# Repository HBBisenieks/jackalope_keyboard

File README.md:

# Jackalope Keyboard

`NOTE:` Current source was built against `ergogen@3.1.1` and will not work with the `4.0.0` release (or newer).

A 50-key ergonomic ~(currently single-piece)~ single-piece or split column-staggered keyboard ~(with a split version planned for the future???)~ inspired by the Absolem, Kryia, and Iris.

The Jackalope layout is focussed on maximizing comfort for the thumbs and reducing reach for the fingers.

## To-Do:
- [x] Finalize prototype PCBs
- [ ] Verify PCBs
- [ ] BOM and build guide
- [ ] Default firmware

## Firmware
The Jackalope can run either [QMK](https://github.com/HBBisenieks/qmk_firmware/tree/jackalope_boards/keyboards/jackalope) 
with a pro-micro or KMK with a KB2040. Default keymap is still a work-in-progress pending 
actual hardware testing.

## Images
Renders of the left and right split PCBs:

## Old images of first-generation monoblock PCB and layout

Built using [Ergogen](https://ergogen.xyz/#).

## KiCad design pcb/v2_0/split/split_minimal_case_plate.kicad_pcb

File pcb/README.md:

# PCBs
The current revision of the boards, both split and monoblock, are under `v2_0/`. As previously, 
these boards are theoretically functional but untested, pending both firmware authoring (QMK and 
KMK support planned) and arrival of the prototype boards from JLCPCB.

## To-Do:
- [ ] Write QMK code
- [ ] Write KMK code
- [ ] Verify PCBs
- [ ] Build guide
- [ ] BOM

~The current revision of PCB uploaded to GH is routed but untested and reflects an older revision of the code than what's available in the base of the repo. It _might_ work, but I honestly put it together to learn a bit more about using KiCad than anything else and haven't yet tested the outline, so, you know, caveat emptor.~

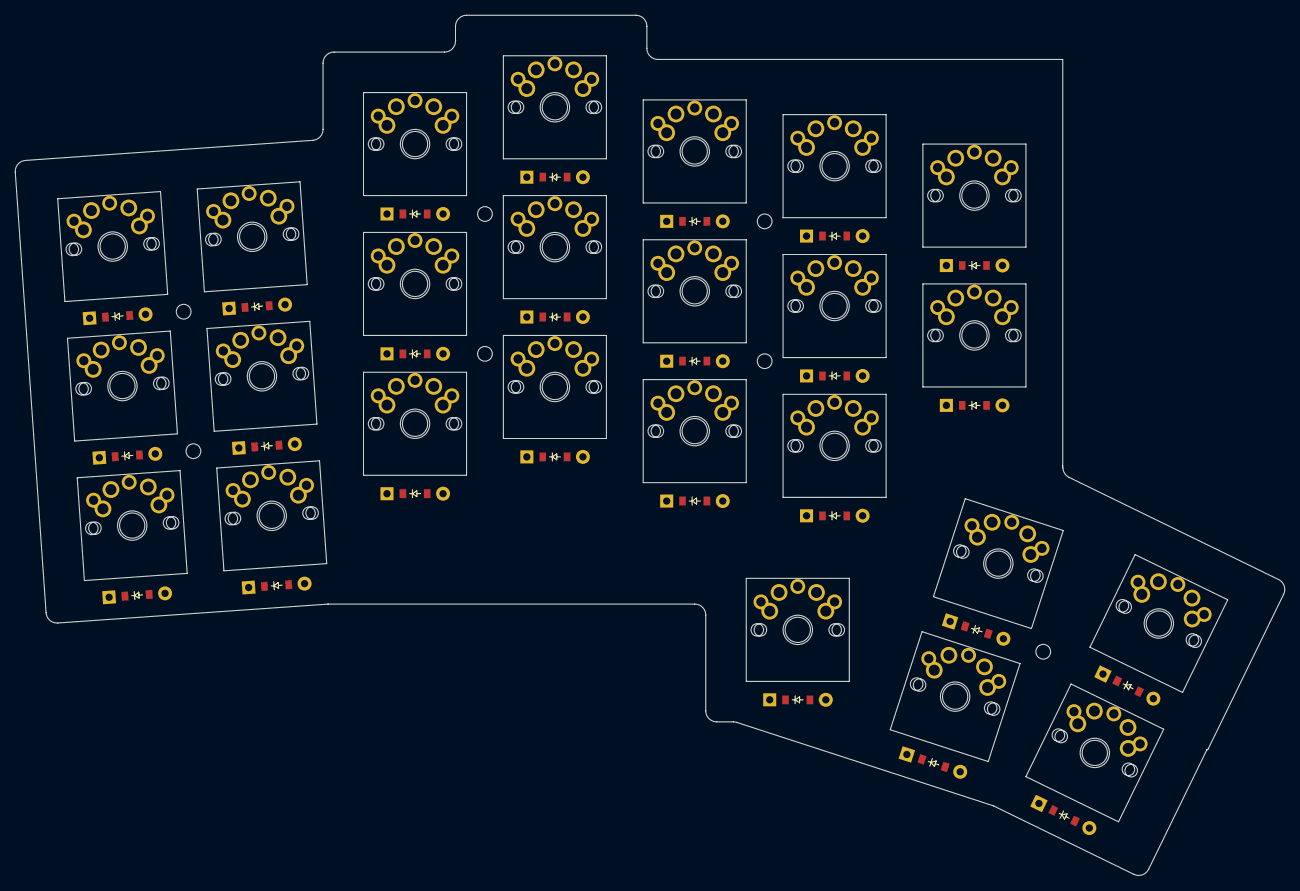
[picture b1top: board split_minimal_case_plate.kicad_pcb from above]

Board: 2 copper layers, 172.5 x 116.9 mm, 75 parts (0 on the bottom side), 36 nets, no tracks yet.

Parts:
D1, D2, D3, D4, D5, D6, D7, D8, D9, D10, D11, D12, D13, D14, D15, D16, D17, D18, D19, D20, D21, D22, D23, D24, D25: ComboDiode
S1, S3, S5, S7, S9, S11, S13, S15, S17, S19, S21, S23, S25, S27, S29, S31, S33, S35, S37, S39, S41, S43, S45, S47, S49: MX
S2, S4, S6, S8, S10, S12, S14, S16, S18, S20, S22, S24, S26, S28, S30, S32, S34, S36, S38, S40, S42, S44, S46, S48, S50: PG1350

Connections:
P0: S7.2, S8.2, S9.2, S10.2, S11.2, S12.2
P1: S1.2, S2.2, S3.2, S4.2, S5.2, S6.2
P2: S13.2, S14.2, S15.2, S16.2, S17.2, S18.2, S41.2, S42.2
P3: S19.2, S20.2, S21.2, S22.2, S23.2, S24.2, S43.2, S44.2
P4: S25.2, S26.2, S27.2, S28.2, S29.2, S30.2, S47.2, S48.2
P5: S31.2, S32.2, S33.2, S34.2, S35.2, S36.2, S45.2, S46.2
P6: S37.2, S38.2, S39.2, S40.2, S49.2, S50.2
P7: D3.1, D3.2, D6.1, D6.2, D9.1, D9.2, D12.1, D12.2, D15.1, D15.2, D18.1, D18.2, D20.1, D20.2
P8: D2.1, D2.2, D5.1, D5.2, D8.1, D8.2, D11.1, D11.2, D14.1, D14.2, D17.1, D17.2, D19.1, D19.2
P9: D1.1, D1.2, D4.1, D4.2, D7.1, D7.2, D10.1, D10.2, D13.1, D13.2, D16.1, D16.2
P10: D21.1, D21.2, D22.1, D22.2, D23.1, D23.2, D24.1, D24.2, D25.1, D25.2
home_lower: D24.1, D24.2, S47.1, S48.1
home_upper: D22.1, D22.2, S43.1, S44.1
index_bottom: D13.1, D13.2, S25.1, S26.1
index_home: D14.1, D14.2, S27.1, S28.1
index_top: D15.1, D15.2, S29.1, S30.1
inner_bottom: D16.1, D16.2, S31.1, S32.1
inner_home: D17.1, D17.2, S33.1, S34.1
inner_top: D18.1, D18.2, S35.1, S36.1
inner_upper: D21.1, D21.2, S41.1, S42.1
macro_home: D19.1, D19.2, S37.1, S38.1
macro_top: D20.1, D20.2, S39.1, S40.1
middle_bottom: D10.1, D10.2, S19.1, S20.1
middle_home: D11.1, D11.2, S21.1, S22.1
middle_top: D12.1, D12.2, S23.1, S24.1
outer_bottom: D1.1, D1.2, S1.1, S2.1
outer_home: D2.1, D2.2, S3.1, S4.1
outer_lower: D25.1, D25.2, S49.1, S50.1
outer_top: D3.1, D3.2, S5.1, S6.1
outer_upper: D23.1, D23.2, S45.1, S46.1
pinky_bottom: D4.1, D4.2, S7.1, S8.1
pinky_home: D5.1, D5.2, S9.1, S10.1
pinky_top: D6.1, D6.2, S11.1, S12.1
ring_bottom: D7.1, D7.2, S13.1, S14.1
ring_home: D8.1, D8.2, S15.1, S16.1
ring_top: D9.1, D9.2, S17.1, S18.1

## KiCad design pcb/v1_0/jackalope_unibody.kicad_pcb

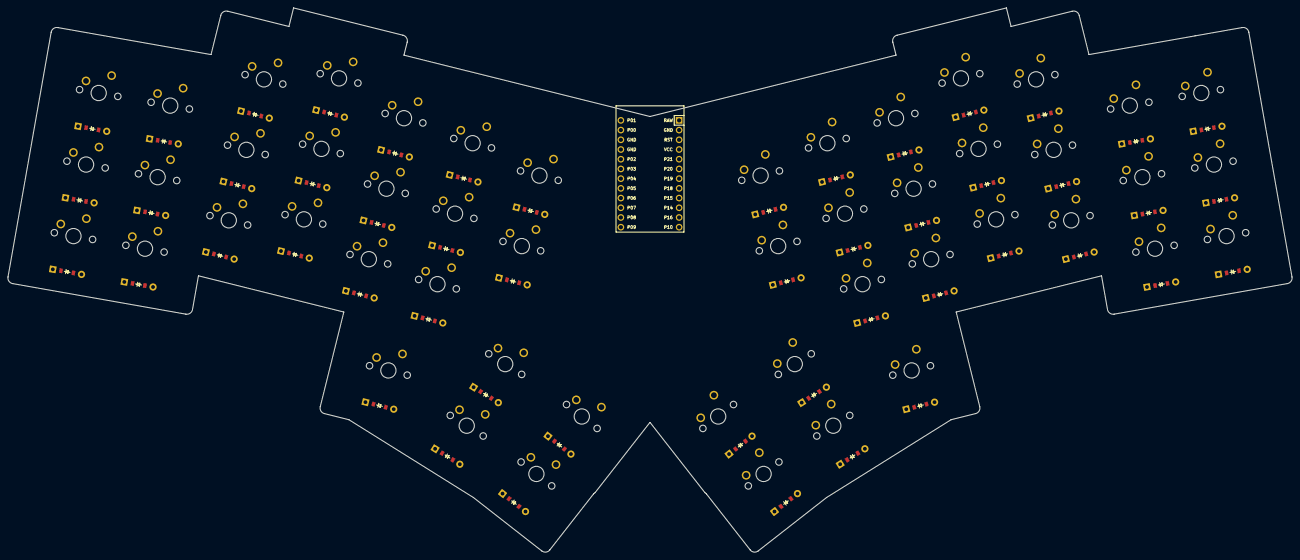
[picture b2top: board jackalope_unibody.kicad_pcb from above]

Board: 2 copper layers, 335.9 x 142.3 mm, 101 parts (0 on the bottom side), 69 nets, no tracks yet.

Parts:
D1, D2, D3, D4, D5, D6, D7, D8, D9, D10, D11, D12, D13, D14, D15, D16, D17, D18, D19, D20, D21, D22, D23, D24, D25, D26, D27, D28, D29, D30, D31, D32, D33, D34, D35, D36, D37, D38, D39, D40, D41, D42, D43, D44, D45, D46, D47, D48, D49, D50: ComboDiode
MCU1: ProMicro
S1, S2, S3, S4, S5, S6, S7, S8, S9, S10, S11, S12, S13, S14, S15, S16, S17, S18, S19, S20, S21, S22, S23, S24, S25, S26, S27, S28, S29, S30, S31, S32, S33, S34, S35, S36, S37, S38, S39, S40, S41, S42, S43, S44, S45, S46, S47, S48, S49, S50: MX

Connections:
GND: MCU1.2, MCU1.15, MCU1.16
P0: MCU1.14, S4.2, S5.2, S6.2
P1: MCU1.13, S1.2, S2.2, S3.2
P2: MCU1.17, S7.2, S8.2, S9.2, S21.2
P3: MCU1.18, S10.2, S11.2, S12.2, S22.2
P4: MCU1.19, S13.2, S14.2, S15.2, S24.2
P5: MCU1.20, S16.2, S17.2, S18.2, S23.2
P6: MCU1.21, S19.2, S20.2, S25.2
P7: D3.1, D3.2, D6.1, D6.2, D9.1, D9.2, D12.1, D12.2, D15.1, D15.2, D18.1, D18.2, D20.1, D20.2, D28.1, D28.2, D31.1, D31.2, D34.1, D34.2, D37.1, D37.2, D40.1, D40.2, D43.1, D43.2, D45.1, D45.2, MCU1.22
P8: D2.1, D2.2, D5.1, D5.2, D8.1, D8.2, D11.1, D11.2, D14.1, D14.2, D17.1, D17.2, D19.1, D19.2, D27.1, D27.2, D30.1, D30.2, D33.1, D33.2, D36.1, D36.2, D39.1, D39.2, D42.1, D42.2, D44.1, D44.2, MCU1.23
P9: D1.1, D1.2, D4.1, D4.2, D7.1, D7.2, D10.1, D10.2, D13.1, D13.2, D16.1, D16.2, D26.1, D26.2, D29.1, D29.2, D32.1, D32.2, D35.1, D35.2, D38.1, D38.2, D41.1, D41.2, MCU1.24
P10: D21.1, D21.2, D22.1, D22.2, D23.1, D23.2, D24.1, D24.2, D25.1, D25.2, D46.1, D46.2, D47.1, D47.2, D48.1, D48.2, D49.1, D49.2, D50.1, D50.2, MCU1.12
P14: MCU1.10, S41.2, S42.2, S43.2, S48.2
P15: MCU1.9, S38.2, S39.2, S40.2, S49.2
P16: MCU1.11, S44.2, S45.2, S50.2
P18: MCU1.8, S35.2, S36.2, S37.2, S47.2
P19: MCU1.7, S32.2, S33.2, S34.2, S46.2
P20: MCU1.6, S29.2, S30.2, S31.2
P21: MCU1.5, S26.2, S27.2, S28.2
home_lower: D24.1, D24.2, S24.1
home_upper: D22.1, D22.2, S22.1
index_bottom: D13.1, D13.2, S13.1
index_home: D14.1, D14.2, S14.1
index_top: D15.1, D15.2, S15.1
inner_bottom: D16.1, D16.2, S16.1
inner_home: D17.1, D17.2, S17.1
inner_top: D18.1, D18.2, S18.1
inner_upper: D21.1, D21.2, S21.1
macro_home: D19.1, D19.2, S19.1
macro_top: D20.1, D20.2, S20.1
middle_bottom: D10.1, D10.2, S10.1
middle_home: D11.1, D11.2, S11.1
middle_top: D12.1, D12.2, S12.1
mirror_home_lower: D49.1, D49.2, S49.1
mirror_home_upper: D47.1, D47.2, S47.1
mirror_index_bottom: D38.1, D38.2, S38.1
mirror_index_home: D39.1, D39.2, S39.1
mirror_index_top: D40.1, D40.2, S40.1
mirror_inner_bottom: D41.1, D41.2, S41.1
mirror_inner_home: D42.1, D42.2, S42.1
mirror_inner_top: D43.1, D43.2, S43.1
mirror_inner_upper: D46.1, D46.2, S46.1
mirror_macro_home: D44.1, D44.2, S44.1
mirror_macro_top: D45.1, D45.2, S45.1
mirror_middle_bottom: D35.1, D35.2, S35.1
mirror_middle_home: D36.1, D36.2, S36.1
mirror_middle_top: D37.1, D37.2, S37.1
mirror_outer_bottom: D26.1, D26.2, S26.1
mirror_outer_home: D27.1, D27.2, S27.1
mirror_outer_lower: D50.1, D50.2, S50.1
mirror_outer_top: D28.1, D28.2, S28.1
mirror_outer_upper: D48.1, D48.2, S48.1
mirror_pinky_bottom: D29.1, D29.2, S29.1
mirror_pinky_home: D30.1, D30.2, S30.1
mirror_pinky_top: D31.1, D31.2, S31.1
mirror_ring_bottom: D32.1, D32.2, S32.1
mirror_ring_home: D33.1, D33.2, S33.1
mirror_ring_top: D34.1, D34.2, S34.1
outer_bottom: D1.1, D1.2, S1.1
outer_home: D2.1, D2.2, S2.1
outer_lower: D25.1, D25.2, S25.1
outer_top: D3.1, D3.2, S3.1
outer_upper: D23.1, D23.2, S23.1
pinky_bottom: D4.1, D4.2, S4.1
pinky_home: D5.1, D5.2, S5.1
pinky_top: D6.1, D6.2, S6.1
ring_bottom: D7.1, D7.2, S7.1
ring_home: D8.1, D8.2, S8.1
ring_top: D9.1, D9.2, S9.1

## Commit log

2022-02-17 added working config file
2022-02-17 add image in readme
2022-02-18 added filler shapes for case
2022-02-18 fix top plates
2022-02-18 change to exterior mounting holes only
2022-02-19 the great renaming
2022-02-19 de-absoleming
2022-02-19 bing broke outline???
2022-02-19 fixed bind outline fuckery
2022-02-19 move diodes down
2022-02-20 replacing thumb cluster 2-row with single row for pcb
2022-02-20 replaced thumb cluster, need to fix binds
2022-02-21 fixed outline, thumb screwhole
2022-02-21 initial pcb commit
2022-02-21 pcb getting prettier
2022-02-21 logo too big and unreadable in dark mode
2022-02-24 begin split work, spelling mistake fixed, gerbers
2022-02-24 screw holes for split
2022-02-25 refining pcb shape
2022-02-25 renaming split/unibody base components
2022-02-25 update screw holes for 1p
2022-02-25 refining case shape for split
2022-02-25 move top screw hole
2022-02-27 fixing screw holes
2022-02-27 more screw-hole stuff idek
2022-02-28 update split middle, extrude split case
2022-02-28 first case commit
2022-02-28 PCB readme
2022-02-28 add controller cutout for 1p middle, move 1p inner top screw holes
2022-03-03 shrink pcb, some tweaks, still incomplete
2022-03-03 fixed gap in outline
2022-03-03 get ready to split (ha!) the code
2022-03-03 duh, put it in source directory
2022-03-03 cleanup of pcb directory
2022-03-03 source readme
2022-03-04 pre-merge pcb
2022-03-04 de-1p-ing split code, not tested at all yet
2022-03-04 de-split code. untested but should work
2022-03-05 re-de-splitting 1p
2022-03-06 updates to split board....again
2022-03-06 updates to monoblock
2022-03-06 de-rotate, fix screw holes, add choc footprints, trrs, mcu
2022-03-06 add chocs to monoblock
2022-03-06 mirror microcontroller
2022-03-06 adding images
2022-03-06 footprints for new silks
2022-03-07 reduce spread of thumb_outer
2022-03-07 reduce spread of outer thumbs on monoblock
2022-03-07 add inner mounting holes
2022-03-07 add minimal plates, inner mounting holes
2022-03-07 minimal case plates
2022-03-07 initial commit of split pcb v2.0
2022-03-13 add inner mounting holes, minimal cases
2022-03-13 screwed up a screw hole
2022-03-13 add inner screw holes to cases
2022-03-13 routed split board, but screw holes screwed up
2022-03-13 case files
2022-03-13 1p pcb files
2022-03-13 update silks
2022-03-13 update pcb file
2022-03-13 remove autosave
2022-03-14 updates to 1p pcb, gerbers
2022-03-14 split pcb routed, gerbers
2022-03-14 update pcb readme
2022-03-14 main readme to-dos
2022-03-15 add: levity
2022-03-15 spacing
2022-03-30 add firmware link for QMK
2023-02-22 update readme as much for a note to myself as anything
2023-02-23 points updated for 4.0
2023-02-24 whatever
2023-02-24 added tray case
2023-02-24 revised wiring, added OLED pads
2023-02-24 updated oled
